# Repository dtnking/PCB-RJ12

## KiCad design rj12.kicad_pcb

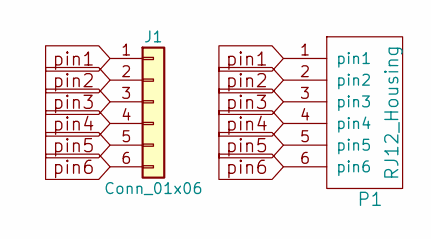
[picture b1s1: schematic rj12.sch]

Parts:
J1: Conn_01x06; Pin_Header_Straight_1x06_Pitch2.54mm
P1: RJ12_Housing; RJ12

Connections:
pin1: J1.1, P1.1
pin2: J1.2, P1.2
pin3: J1.3, P1.3
pin4: J1.4, P1.4
pin5: J1.5, P1.5
pin6: J1.6, P1.6

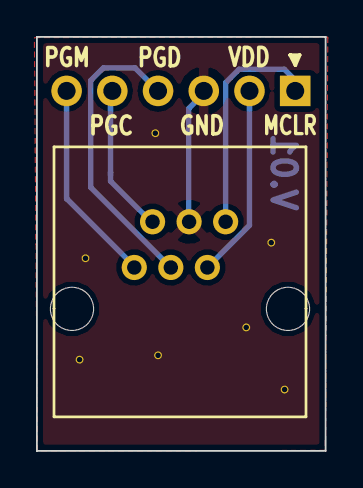
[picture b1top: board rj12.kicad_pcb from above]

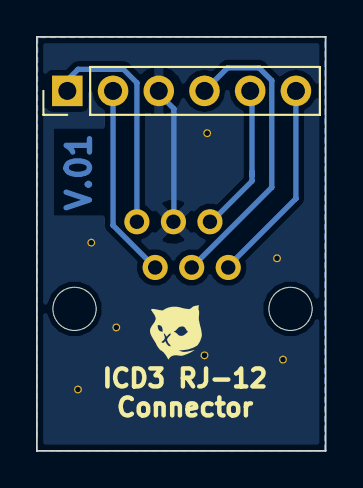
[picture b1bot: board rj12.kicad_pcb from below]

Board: 2 copper layers, 16.0 x 23.0 mm, 3 parts (2 on the bottom side), 6 nets.

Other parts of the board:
Kitty: G***; Kitty

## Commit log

2017-10-03 PCB design of RJ12
2017-10-03 Added Gerber File
2017-10-12 Re-design the rj12 housing
2017-10-13 re-designed housing
2017-10-24 Copper-Poured with Pin3 and placed the indicator closer to the pin
2017-11-07 Change the size of text to 0.8 x 1.0 mm
2017-11-14 Change the outline more compact
2017-11-15 Added a txt V.01 to indicate version 1 and added gerber file to be panelized
2017-11-16 Moved edge label further inward
2017-11-16 Changed the size of NPTH and PTH from 0.5 to 2.4 and 0.6 to 0.8 mm respectively.
2017-11-18 Added copper poured with via stiching
2017-11-20 Generated new gerber files
2017-12-03 Changed the kitty logo
2017-12-10 Change the clearance of copper pour to 0.3mm
